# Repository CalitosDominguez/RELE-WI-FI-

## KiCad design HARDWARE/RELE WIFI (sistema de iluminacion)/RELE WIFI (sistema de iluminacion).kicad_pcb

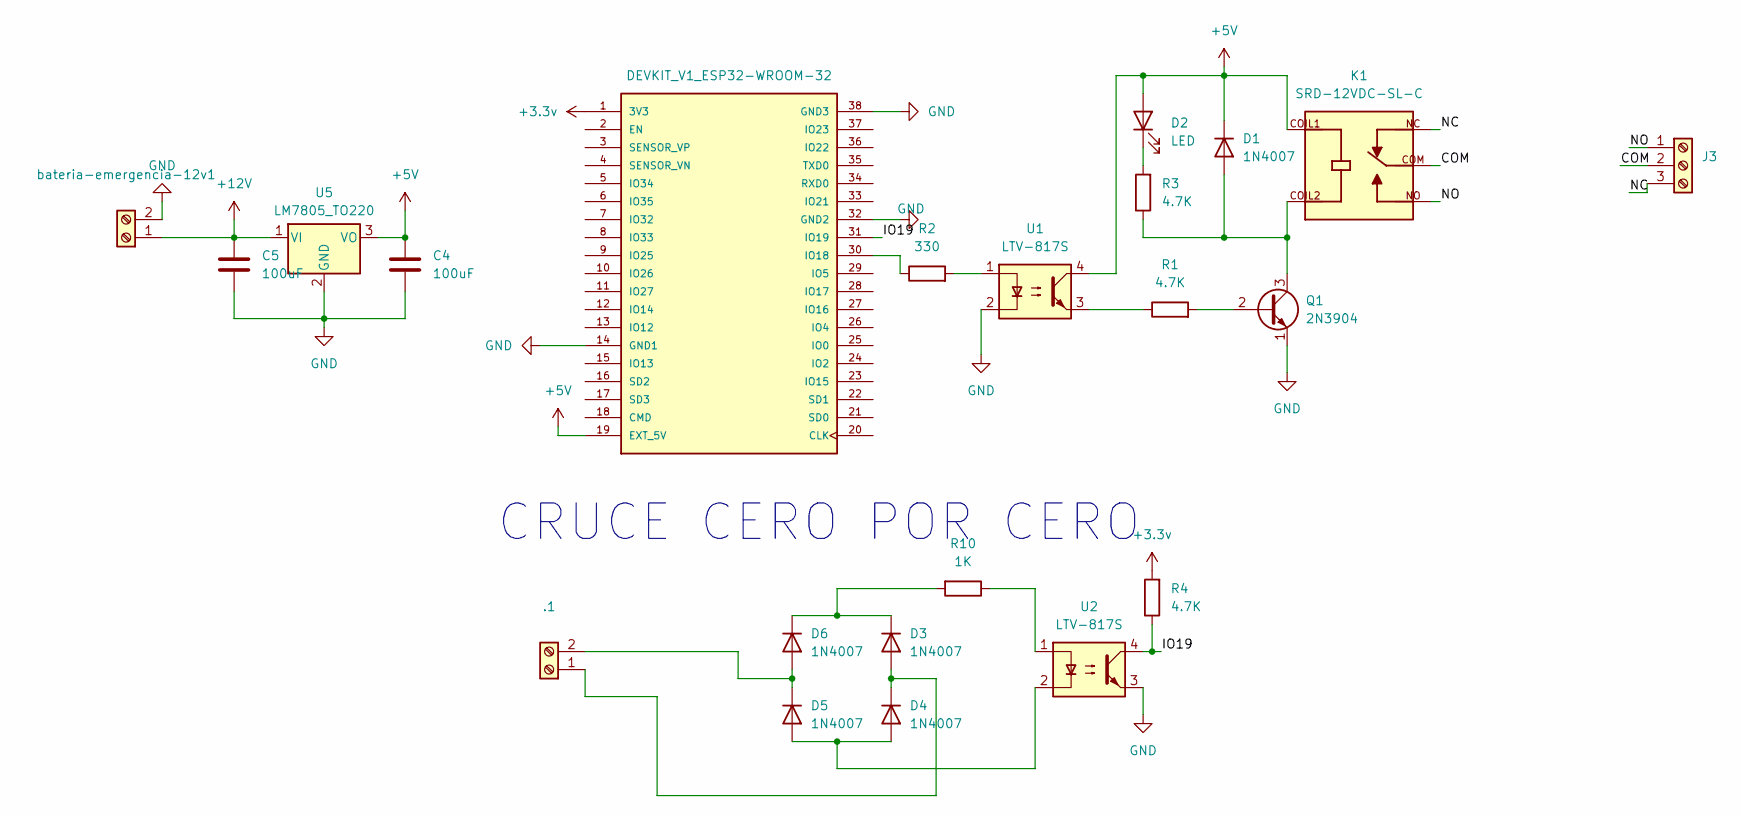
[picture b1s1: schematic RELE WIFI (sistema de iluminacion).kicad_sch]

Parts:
.1: Screw_Terminal_01x02; TerminalBlock_MaiXu_MX126-5.0-02P_1x02_P5.00mm
C4, C5: 100uF
D1, D3, D4, D5, D6: 1N4007; D_A-405_P7.62mm_Horizontal
D2: LED; LED_D1.8mm_W3.3mm_H2.4mm
J3: Screw_Terminal_01x03; TerminalBlock_MaiXu_MX126-5.0-03P_1x03_P5.00mm
K1: SRD-12VDC-SL-C; RELAY_SRD-12VDC-SL-C; PARTREV 1.0
Q1: 2N3904; TO-92_Inline
R1: 4.7K; R_0805_2012Metric_Pad1.20x1.40mm_HandSolder
R2: 330; R_0805_2012Metric_Pad1.20x1.40mm_HandSolder
R3, R4: 4.7K; R_0805_2012Metric
R10: 1K; R_0805_2012Metric_Pad1.20x1.40mm_HandSolder
U1, U2: LTV-817S; SMDIP-4_W9.53mm
U3: DEVKIT_V1_ESP32-WROOM-32; MODULE_DEVKIT_V1_ESP32-WROOM-32; PARTREV N/A
U5: LM7805_TO220; TO-220-3_Vertical
bateria-emergencia-12v1: Screw_Terminal_01x02

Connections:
+3.3v: R4.2, U3.1 (3V3)
+5V: C4.2, D1.1 (K), D2.2 (A), K1.COIL1, U1.4, U3.19 (EXT_5V), U5.3 (VO)
+12V: C5.2, U5.1 (VI), bateria-emergencia-12v1.1
/COM: J3.2, K1.COM
/IO19: R4.1, U2.4, U3.31 (IO19)
/NC: J3.3, K1.NC
/NO: J3.1, K1.NO
GND: C4.1, C5.1, Q1.1 (E), U1.2, U2.3, U3.14 (GND1), U3.32 (GND2), U3.38 (GND3), U5.2 (GND), bateria-emergencia-12v1.2
unnamed: .1.1, D3.2 (A), D4.1 (K)
unnamed: .1.2, D5.1 (K), D6.2 (A)
unnamed: D1.2 (A), K1.COIL2, Q1.3 (C), R3.1
unnamed: D2.1 (K), R3.2
unnamed: D3.1 (K), D6.1 (K), R10.2
unnamed: D4.2 (A), D5.2 (A), U2.2
unnamed: Q1.2 (B), R1.2
unnamed: R1.1, U1.3
unnamed: R2.2, U1.1
unnamed: R10.1, U2.1
unnamed: R2.1, U3.30 (IO18)

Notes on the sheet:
CRUCE CERO POR CERO

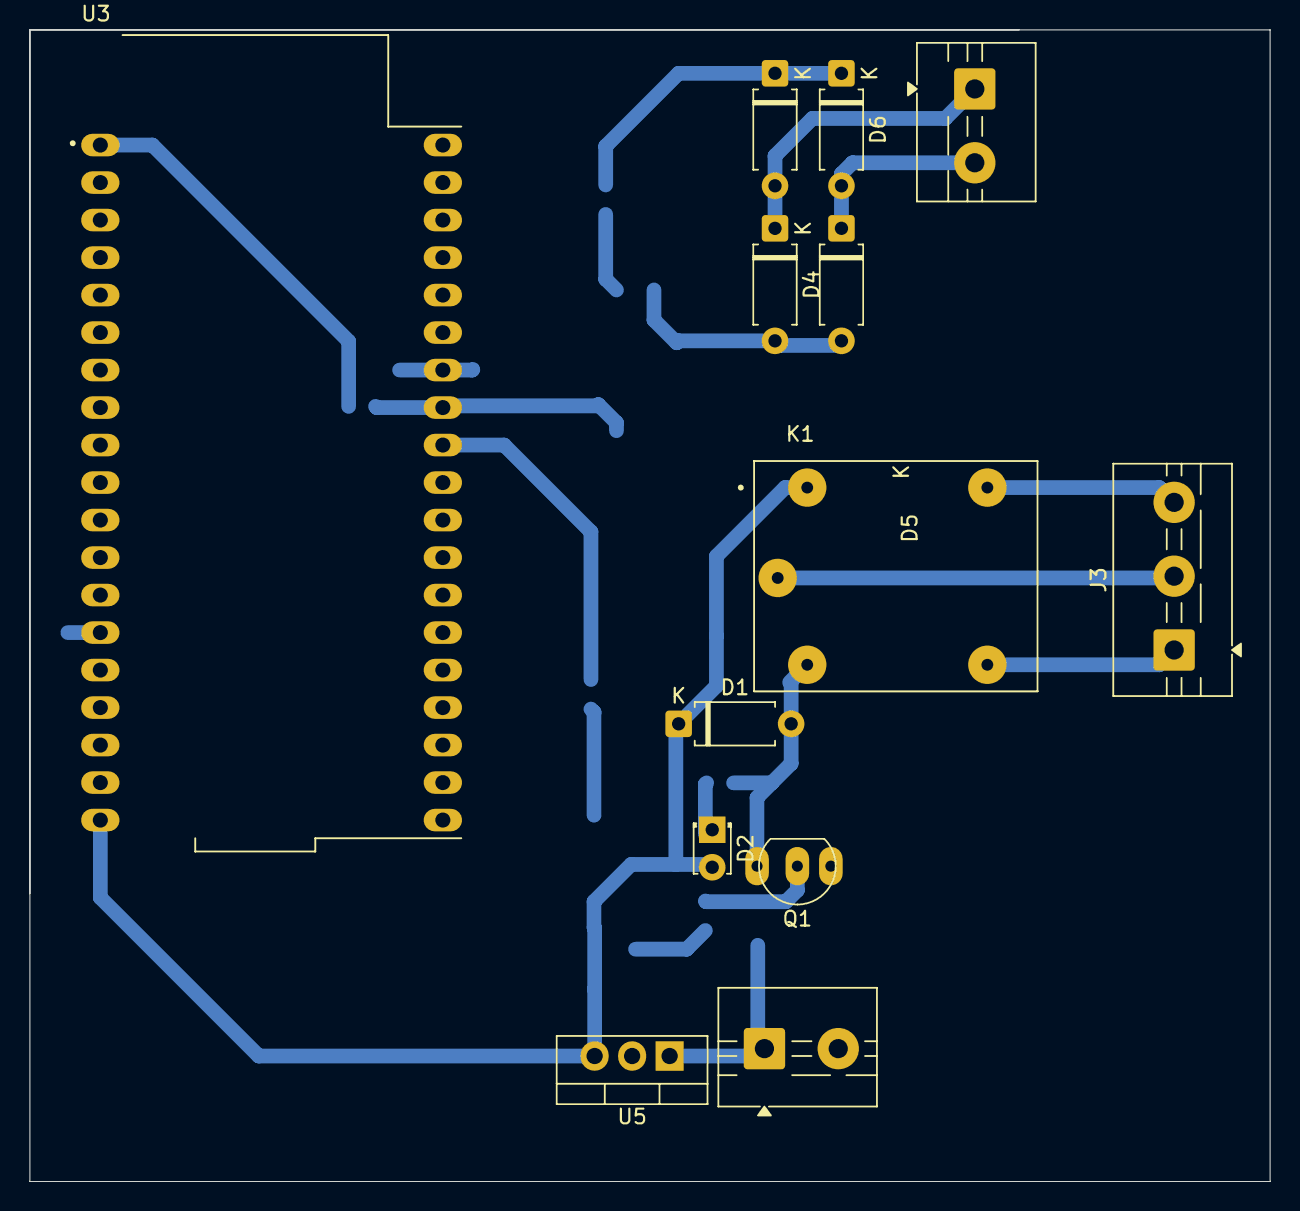
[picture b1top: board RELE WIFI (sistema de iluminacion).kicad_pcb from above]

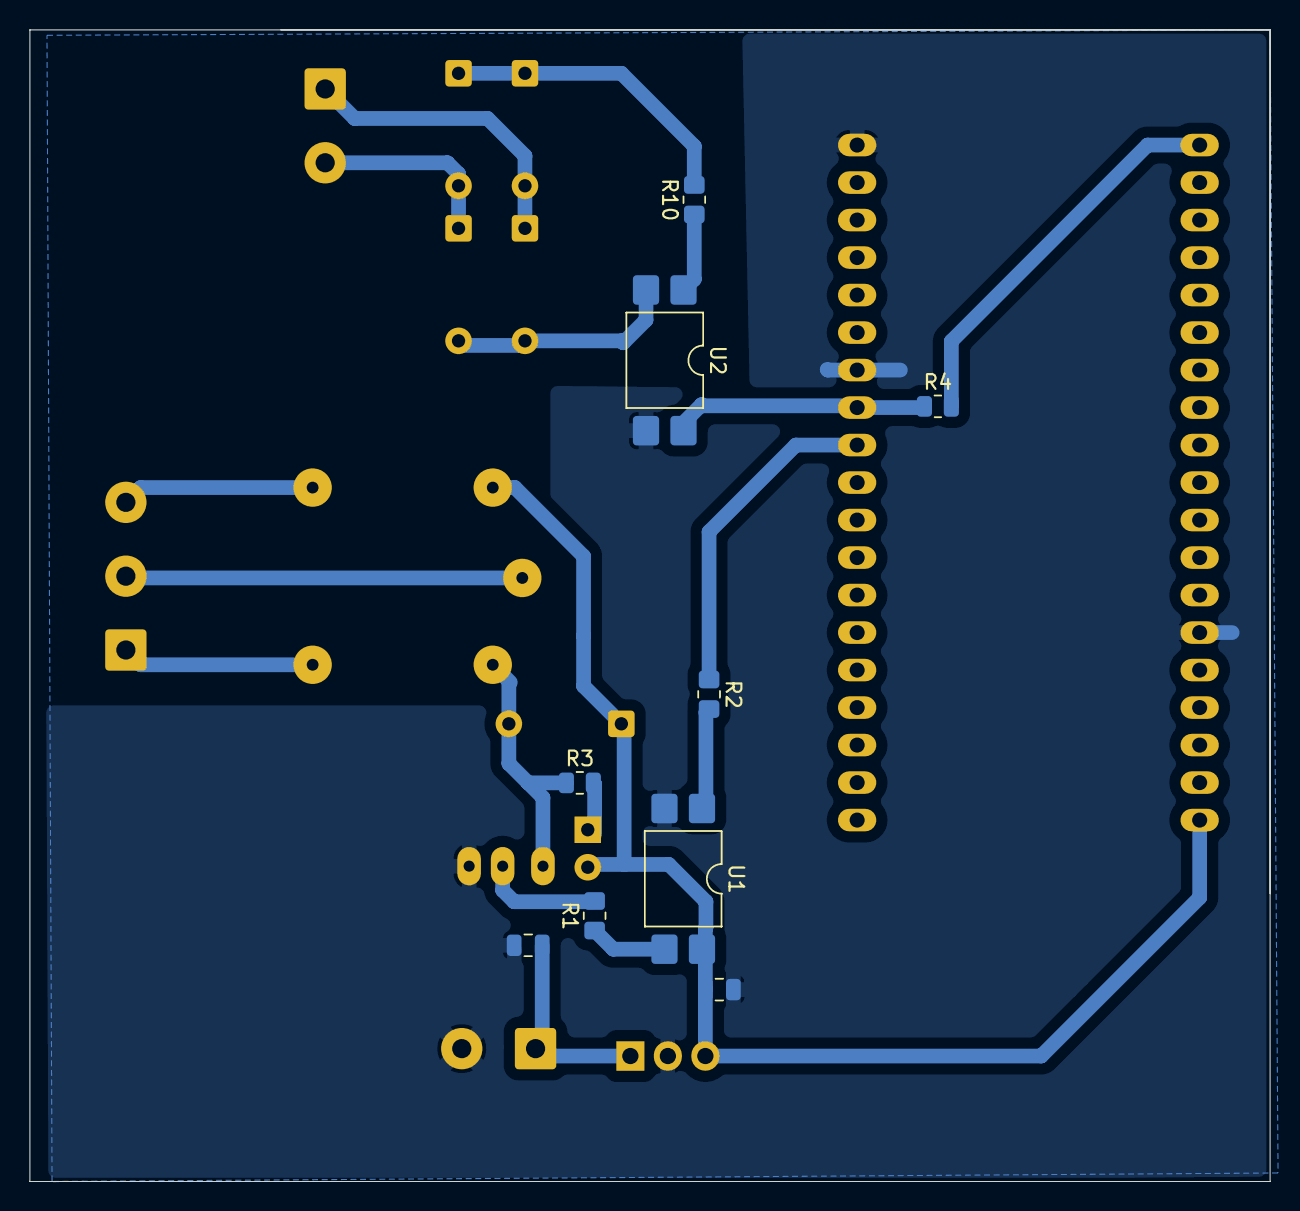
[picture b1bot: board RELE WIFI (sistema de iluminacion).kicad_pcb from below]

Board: 2 copper layers, 84.0 x 78.0 mm, 22 parts (9 on the bottom side), 19 nets.
